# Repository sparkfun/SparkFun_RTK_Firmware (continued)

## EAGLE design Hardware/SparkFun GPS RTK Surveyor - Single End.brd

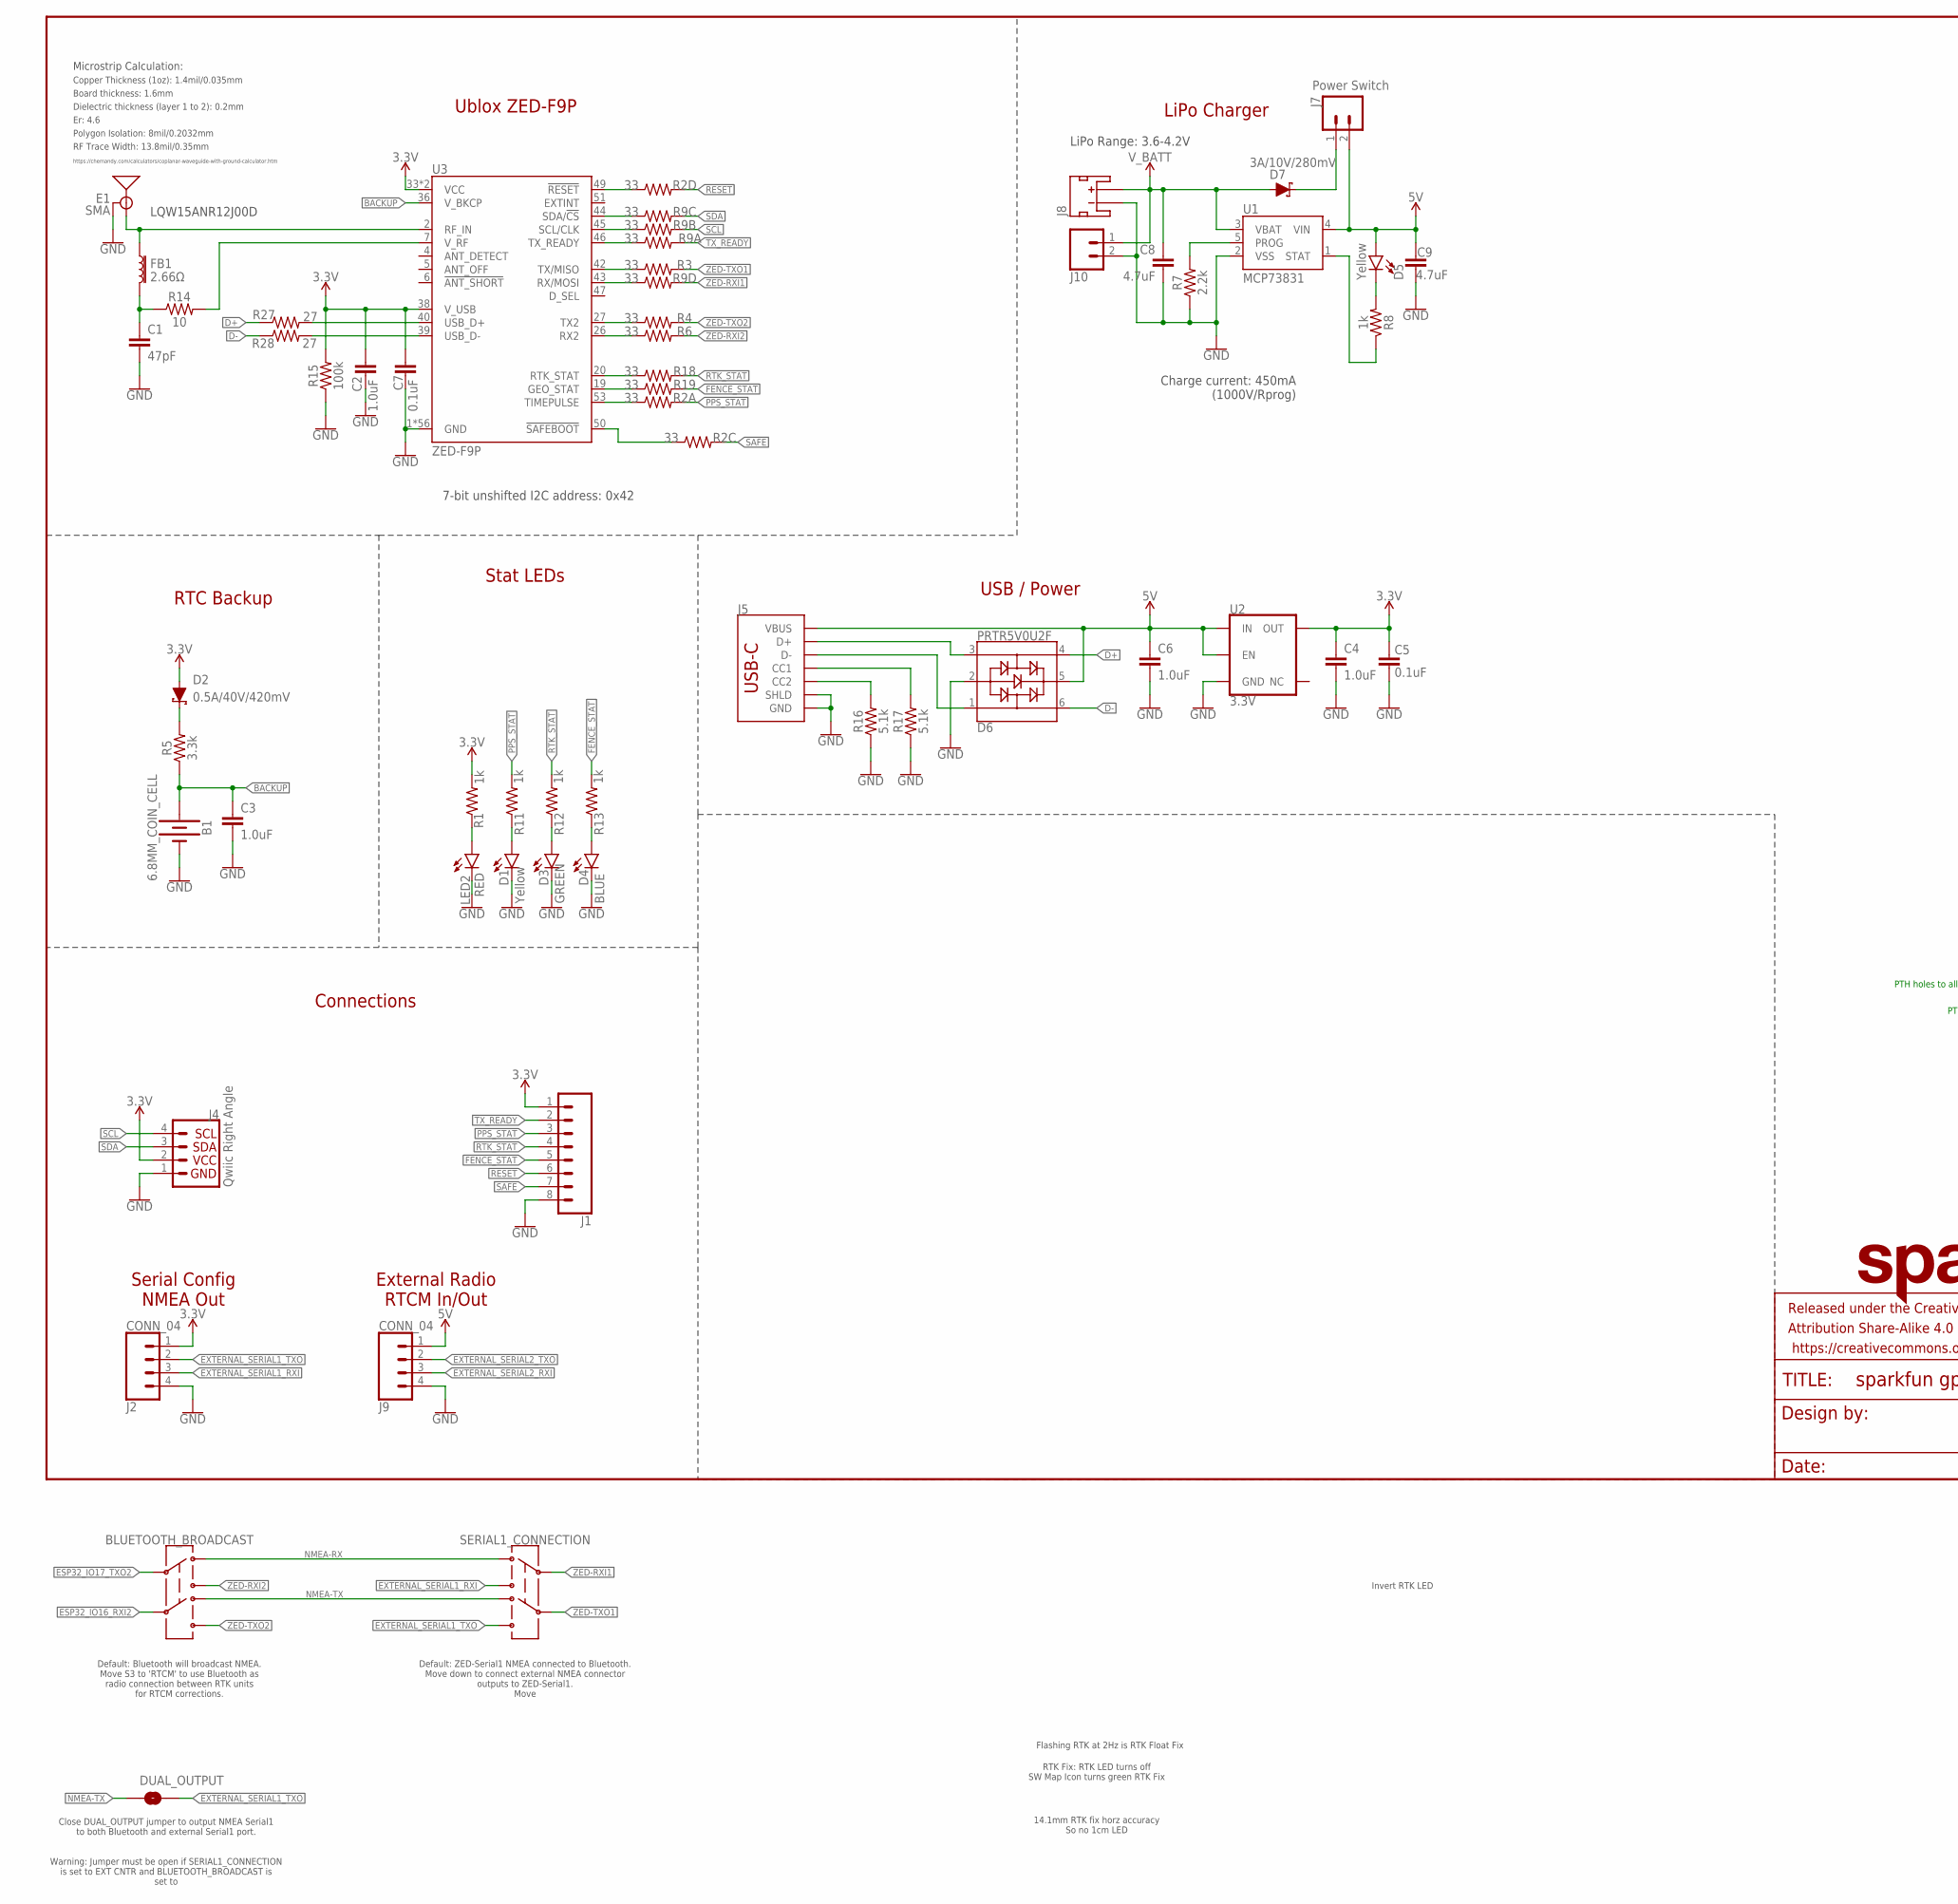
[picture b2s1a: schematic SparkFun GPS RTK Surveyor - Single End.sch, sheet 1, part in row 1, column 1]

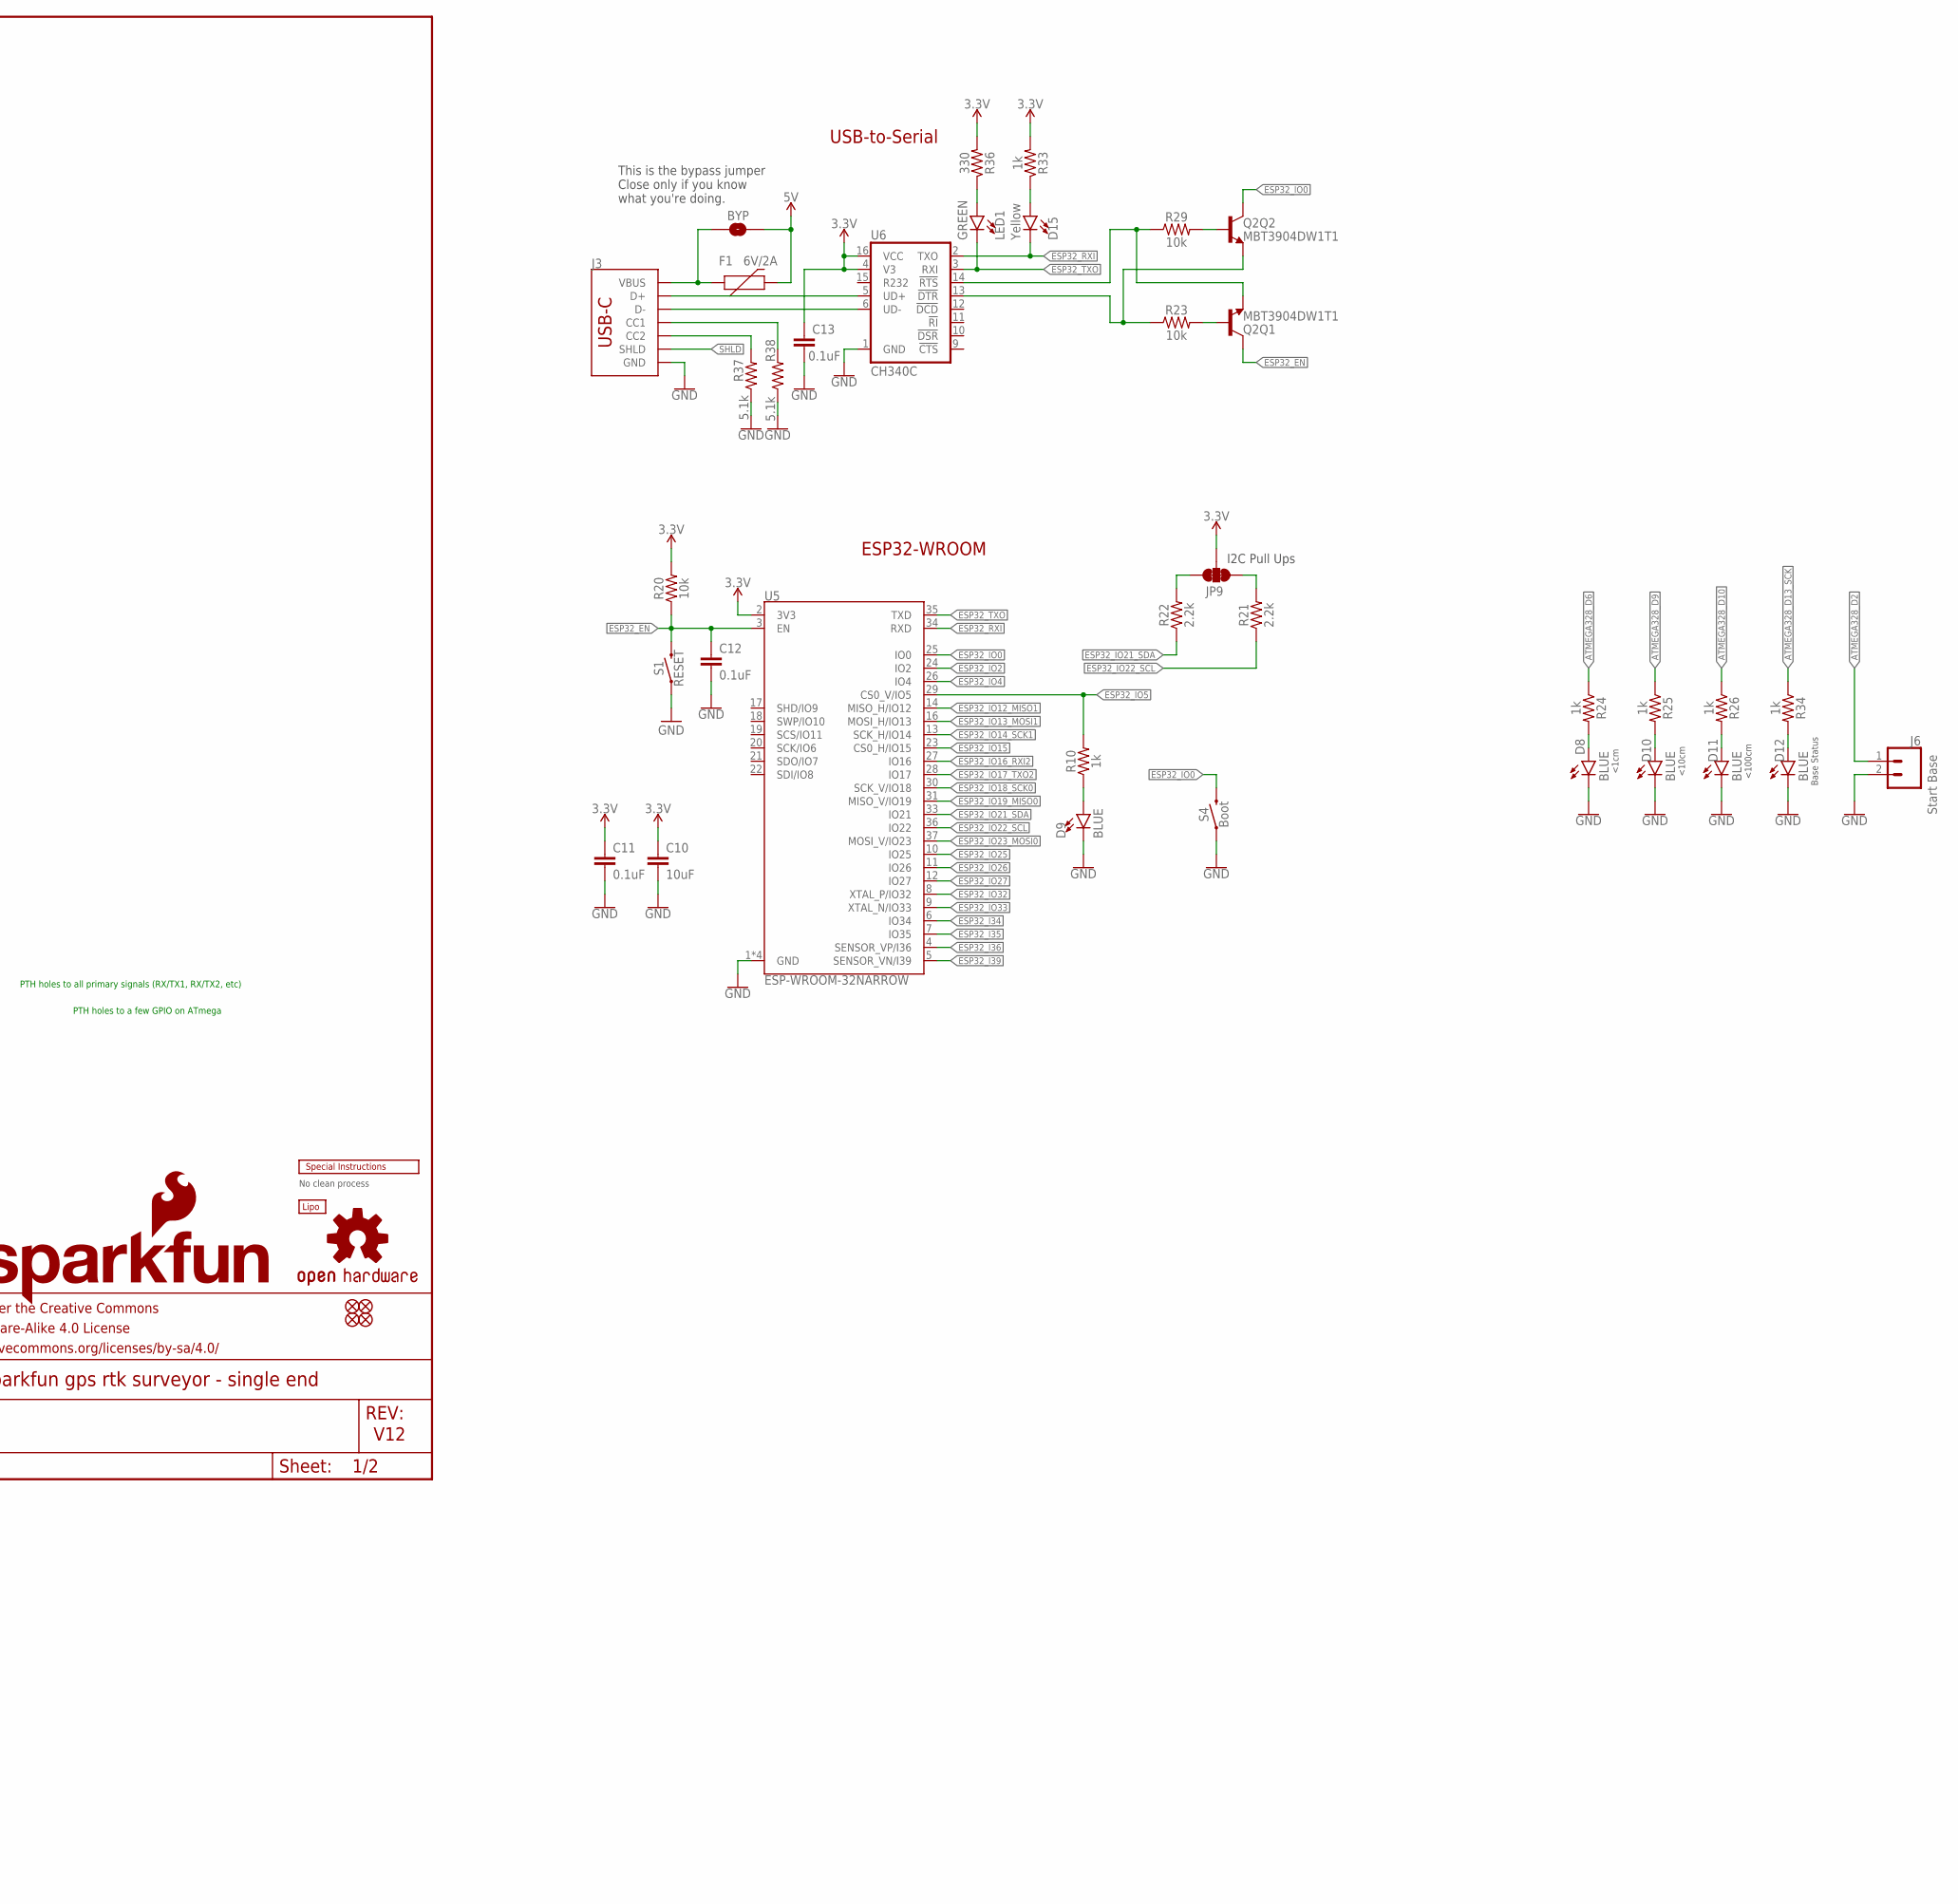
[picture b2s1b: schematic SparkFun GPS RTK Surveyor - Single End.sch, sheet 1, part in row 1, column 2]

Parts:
B1: 6.8MM_COIN_CELL; ML414H_IV01E
BLUETOOTH_BROADCAST: SWITCH-DPDT-SMD-AYZ0202; SWITCH_DPDT_SMD_AYZ0202
BT1: LIPO-OUTLINE1100; LIPO-1000
BYP: JUMPER-SMT_2_NO_SILK; SMT-JUMPER_2_NO_SILK
C1: 47pF; 0402
C2, C3, C4, C6: 1.0uF; 0603
C5, C7, C11, C12, C13: 0.1uF; 0603
C8, C9: 4.7uF; 0603
C10: 10uF; 0603
D1, D5, D15: Yellow; LED-0603
D2: 0.5A/40V/420mV; SOD-323
D3: GREEN; LED-0603
D4, D8, D9, D10, D11, D12: BLUE; LED-0603
D6: PRTR5V0U2F; SOT886
D7: 3A/10V/280mV; SOD-323
DUAL_OUTPUT: JUMPER-SMT_2_NO_SILK; SMT-JUMPER_2_NO_SILK
E1: SMA; SMA-EDGE-SMD
F1: 6V/2A; 1210
FB1: 2.66Ω; 0402-TIGHT
FRAME2: FRAME-LEDGER; CREATIVE_COMMONS
J1: CONN_08NO_SILK_DNP; 1X08_NO_SILK
J2, J9: CONN_04; JST-4-SMD-1.25MM-LOCKING
J3: USB-C; USB-C-16P-2LAYER-PADS
J4: Qwiic Right Angle; JST04_1MM_RA
J5: USB_C_2-LAYER_PADS; USB-C-16P-2LAYER-PADS
J6: Start Base; JST-2-SMD
J7: Power Switch; JST-2-SMD
J8: JST_2MM_MALE; JST-2-SMD
J10: CONN_021X02_NO_SILK; 1X02_NO_SILK
JP9: JUMPER-SMT_3_2-NC_TRACE_SILK; SMT-JUMPER_3_2-NC_TRACE_SILK
JP21, JP61, JP71, JP81: FIDUCIALUFIDUCIAL; MICRO-FIDUCIAL
LED1: GREEN; LED-0603
LED2: RED; LED-0603
LOGO1: OSHW-LOGOMINI; OSHW-LOGO-MINI
LOGO2: SFE_LOGO_NAME_FLAME.1_INCH; SFE_LOGO_NAME_FLAME_.1
Q2: MBT3904DW1T1; SC70-6
R1, R8, R10, R11, R12, R13, R24, R25, R26, R33, R34: 1k; 0603
R2, R9: 33; 1206_RA
R3, R4, R6, R18, R19: 33; 0603
R5: 3.3k; 0603
R7, R21, R22: 2.2k; 0603
R14: 10; 0603
R15: 100k; 0603
R16, R17, R37, R38: 5.1k; 0603
R20, R23, R29: 10k; 0603
R27, R28: 27; 0603
R36: 330; 0603
S1: RESET; TACTILE_SWITCH_SMD_6.0X3.5MM
S4: Boot; TACTILE_SWITCH_SMD_6.0X3.5MM
SERIAL1_CONNECTION: SWITCH-DPDT-SMD-AYZ0202; SWITCH_DPDT_SMD_AYZ0202
U1: MCP73831; SOT23-5
U2: 3.3V; SOT23-5
U3: ZED-F9P
U5: ESP-WROOM-32NARROW; ESP-WROOM-32-NARROW
U6: CH340C; SO016
U$2: SPECIAL_INSTRUCTIONS-ORDERING; ORDERING_INSTRUCTIONS

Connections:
3.3V: C2.1, C4.1, C5.2, C7.2, C10.1, C11.1, C13.1, D2.A, J1.1, J2.1, J4.2, JP9.2, R1.2, R15.2, R20.2, R33.2, R36.2, U2.5 (OUT), U3.33 (VCC), U3.34 (VCC), U3.38 (V_USB), U5.2 (3V3), U6.4 (V3), U6.16 (VCC)
5V: BYP.2, C6.1, C9.1, D5.A, D6.5, F1.2, J5.VBUS1 (VBUS), J5.VBUS2 (VBUS), J7.2 (1), J9.1, U1.4 (VIN), U2.1 (IN), U2.3 (EN)
!RESET: J1.6, R2.P5 (2)
!SAFE: J1.7, R2.P6 (2)
ANT_VCC: C1.1, FB1.2, R14.1
ATMEGA328_D2: J6.1 (2)
ATMEGA328_D6: R24.1
ATMEGA328_D9: R25.1
ATMEGA328_D10: R26.1
ATMEGA328_D13_SCK: R34.1
BACKUP: B1.+, C3.1, R5.1, U3.36 (V_BKCP)
CC1: J5.A5 (CC1), R17.2
CC2: J5.B5 (CC2), R16.2
CC3: J3.B5 (CC2), R37.2
CC4: J3.A5 (CC1), R38.2
CHG_LED: R8.1, U1.1 (STAT)
D+: D6.4, R27.1
D+1: J3.A6 (D+), J3.B6 (D+), U6.5 (UD+)
D-: D6.6, R28.1
D-1: J3.A7 (D-), J3.B7 (D-), U6.6 (UD-)
ESP32_!DTR: Q2.1 (E), R23.1, U6.13 (!DTR)
ESP32_!RTS: Q2.4 (E), R29.1, U6.14 (!RTS)
ESP32_EN: C12.1, Q2.3 (C), R20.1, S1.2, U5.3 (EN)
ESP32_I34: U5.6 (IO34)
ESP32_I35: U5.7 (IO35)
ESP32_I36: U5.4 (SENSOR_VP/I36)
ESP32_I39: U5.5 (SENSOR_VN/I39)
ESP32_IO0: Q2.6 (C), S4.2, U5.25 (IO0)
ESP32_IO2: U5.24 (IO2)
ESP32_IO4: U5.26 (IO4)
ESP32_IO5: R10.2, U5.29 (CS0_V/IO5)
ESP32_IO12_MISO1: U5.14 (MISO_H/IO12)
ESP32_IO13_MOSI1: U5.16 (MOSI_H/IO13)
ESP32_IO14_SCK1: U5.13 (SCK_H/IO14)
ESP32_IO15: U5.23 (CS0_H/IO15)
ESP32_IO16_RXI2: BLUETOOTH_BROADCAST.5, U5.27 (IO16)
ESP32_IO17_TXO2: BLUETOOTH_BROADCAST.2, U5.28 (IO17)
ESP32_IO18_SCK0: U5.30 (SCK_V/IO18)
ESP32_IO19_MISO0: U5.31 (MISO_V/IO19)
ESP32_IO21_SDA: R22.1, U5.33 (IO21)
ESP32_IO22_SCL: R21.1, U5.36 (IO22)
ESP32_IO23_MOSI0: U5.37 (MOSI_V/IO23)
ESP32_IO25: U5.10 (IO25)
ESP32_IO26: U5.11 (IO26)
ESP32_IO27: U5.12 (IO27)
ESP32_IO32: U5.8 (XTAL_P/IO32)
ESP32_IO33: U5.9 (XTAL_N/IO33)
ESP32_RXI: D15.C, U5.34 (RXD), U6.2 (TXO)
ESP32_TXO: LED1.C, U5.35 (TXD), U6.3 (RXI)
EXTERNAL_SERIAL1_RXI: J2.3, SERIAL1_CONNECTION.3
EXTERNAL_SERIAL1_TXO: DUAL_OUTPUT.2, J2.2, SERIAL1_CONNECTION.6
EXTERNAL_SERIAL2_RXI: J9.3
EXTERNAL_SERIAL2_TXO: J9.2
FENCE_STAT: J1.5, R13.2, R19.2
GND: B1.-, C1.2, C2.2, C3.2, C4.2, C5.1, C6.2, C7.1, C8.2, C9.2, C10.2, C11.2, C12.2, C13.2, D1.C, D3.C, D4.C, D6.2, D8.C, D9.C, D10.C, D11.C, D12.C, E1.GND@0 (GND), E1.GND@1 (GND), J1.8, J2.4, J3.GND, J3.GND2 (GND), J4.1, J5.GND, J5.GND2 (GND), J5.SHLD1 (SHLD), J5.SHLD2 (SHLD), J5.SHLD3 (SHLD), J5.SHLD4 (SHLD), J6.2 (1), J8.1 (-), J9.4, J10.2, LED2.C, R7.1, R15.1, R16.1, R17.1, R37.1, R38.1, S1.1, S4.1, U1.2 (VSS), U2.2 (GND), U3.1 (GND), U3.3 (GND), U3.12 (GND), U3.14 (GND), U3.32 (GND), U3.37 (GND), U3.41 (GND), U3.48 (GND), U3.55 (GND), U3.56 (GND), U3.57 (GND), U3.58 (GND), U3.59 (GND), U3.60 (GND), U3.61 (GND), U3.62 (GND), U3.63 (GND), U3.64 (GND), U3.65 (GND), U3.66 (GND), U3.67 (GND), U3.68 (GND), U3.69 (GND), U3.70 (GND), U3.71 (GND), U3.72 (GND), U3.73 (GND), U3.74 (GND), U3.75 (GND), U3.76 (GND), U3.77 (GND), U3.78 (GND), U3.79 (GND), U3.80 (GND), U3.81 (GND), U3.82 (GND), U3.83 (GND), U3.84 (GND), U3.85 (GND), U3.86 (GND), U3.87 (GND), U3.88 (GND), U3.89 (GND), U3.90 (GND), U3.91 (GND), U3.92 (GND), U3.93 (GND), U3.94 (GND), U3.95 (GND), U3.96 (GND), U3.97 (GND), U3.98 (GND), U3.99 (GND), U3.100 (GND), U3.101 (GND), U3.102 (GND), U5.1 (GND), U5.15 (GND), U5.38 (GND), U5.GND, U6.1 (GND)
GPS_ANT1: E1.SIG (SIGNAL), FB1.1, U3.2 (RF_IN)
unnamed: D3.A, R12.1
unnamed: D1.A, R11.1
unnamed: R7.2, U1.5 (PROG)
unnamed: D2.C, R5.2
unnamed: D4.A, R13.1
unnamed: D5.C, R8.2
unnamed: LED2.A, R1.1
unnamed: R27.2, U3.40 (USB_D+)
unnamed: R28.2, U3.39 (USB_D-)
unnamed: R14.2, U3.7 (V_RF)
unnamed: R6.1, U3.26 (RX2)
unnamed: R2.P4 (1), U3.49 (!RESET!)
unnamed: R2.P3 (1), U3.50 (!SAFEBOOT!)
unnamed: R18.1, U3.20 (RTK_STAT)
unnamed: R19.1, U3.19 (GEO_STAT)
unnamed: R9.P1 (1), U3.46 (TX_READY)
unnamed: D9.A, R10.1
unnamed: Q2.5 (B), R23.2
unnamed: Q2.2 (B), R29.2
unnamed: D8.A, R24.2
unnamed: D10.A, R25.2
unnamed: LED1.A, R36.1
unnamed: D11.A, R26.2
unnamed: D12.A, R34.2
unnamed: D15.A, R33.1
unnamed: BYP.1, F1.1, J3.VBUS1 (VBUS), J3.VBUS2 (VBUS)
NMEA-RX: BLUETOOTH_BROADCAST.1, SERIAL1_CONNECTION.1
NMEA-TX: BLUETOOTH_BROADCAST.4, DUAL_OUTPUT.1, SERIAL1_CONNECTION.4
PPS: R2.P1 (1), U3.53 (TIMEPULSE)
PPS_STAT: J1.3, R2.P8 (2), R11.2
RTK_STAT: J1.4, R12.2, R18.2
RXLV: R9.P4 (1), U3.43 (RX/MOSI)
SCL: J4.4, R9.P7 (2)
SCL_LV: R9.P2 (1), U3.45 (SCL/CLK)
SCL_PU1: JP9.1, R21.2
SDA: J4.3, R9.P6 (2)
SDA_LV: R9.P3 (1), U3.44 (SDA/!CS!)
SDA_PU1: JP9.3, R22.2
SHLD: J3.SHLD1 (SHLD), J3.SHLD2 (SHLD), J3.SHLD3 (SHLD), J3.SHLD4 (SHLD)
TX2_P: R4.1, U3.27 (TX2)
TXLV: R3.1, U3.42 (TX/MISO)
TX_READY: J1.2, R9.P8 (2)
UNP_D+: D6.3, J5.A6 (D+), J5.B6 (D+)
UNP_D-: D6.1, J5.A7 (D-), J5.B7 (D-)
VBATT_SWTICHED: D7.C, J7.1 (2)
V_BATT: C8.1, D7.A, J8.2 (+), J10.1, U1.3 (VBAT)
ZED-RXI1: R9.P5 (2), SERIAL1_CONNECTION.2
ZED-RXI2: BLUETOOTH_BROADCAST.3, R6.2
ZED-TXO1: R3.2, SERIAL1_CONNECTION.5
ZED-TXO2: BLUETOOTH_BROADCAST.6, R4.2

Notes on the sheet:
V12
7-bit unshifted I2C address: 0x42
Ublox ZED-F9P
RTC Backup
Stat LEDs
LQW15ANR12J00D
Board thickness: 1.6mm
Er: 4.6
Copper Thickness (1oz): 1.4mil/0.035mm
RF Trace Width: 13.8mil/0.35mm
Polygon Isolation: 8mil/0.2032mm
No clean process
Dielectric thickness (layer 1 to 2): 0.2mm
https://chemandy.com/calculators/coplanar-waveguide-with-ground-calculator.htm
Microstrip Calculation:
Connections
USB / Power
External Radio RTCM In/Out
Serial Config NMEA Out
LiPo Charger
LiPo Range: 3.6-4.2V
Charge current: 450mA (1000V/Rprog)
Base Status
<100cm
<10cm
<1cm
PTH holes to all primary signals (RX/TX1, RX/TX2, etc)
PTH holes to a few GPIO on ATmega
Default: Bluetooth will broadcast NMEA. Move S3 to 'RTCM' to use Bluetooth as radio connection between RTK units for RTCM corrections.
Default: ZED-Serial1 NMEA connected to Bluetooth. Move down to connect external NMEA connector outputs to ZED-Serial1. Move
Close DUAL_OUTPUT jumper to output NMEA Serial1 to both Bluetooth and external Serial1 port. Warning: Jumper must be open if SERIAL1_CONNECTION is set to EXT CNTR and BLUETOOTH_BROADCAST is set to
Flashing RTK at 2Hz is RTK Float Fix
RTK Fix: RTK LED turns off SW Map Icon turns green RTK Fix
Invert RTK LED
14.1mm RTK fix horz accuracy So no 1cm LED
ESP32-WROOM
I2C Pull Ups
USB-to-Serial
This is the bypass jumper Close only if you know what you're doing.

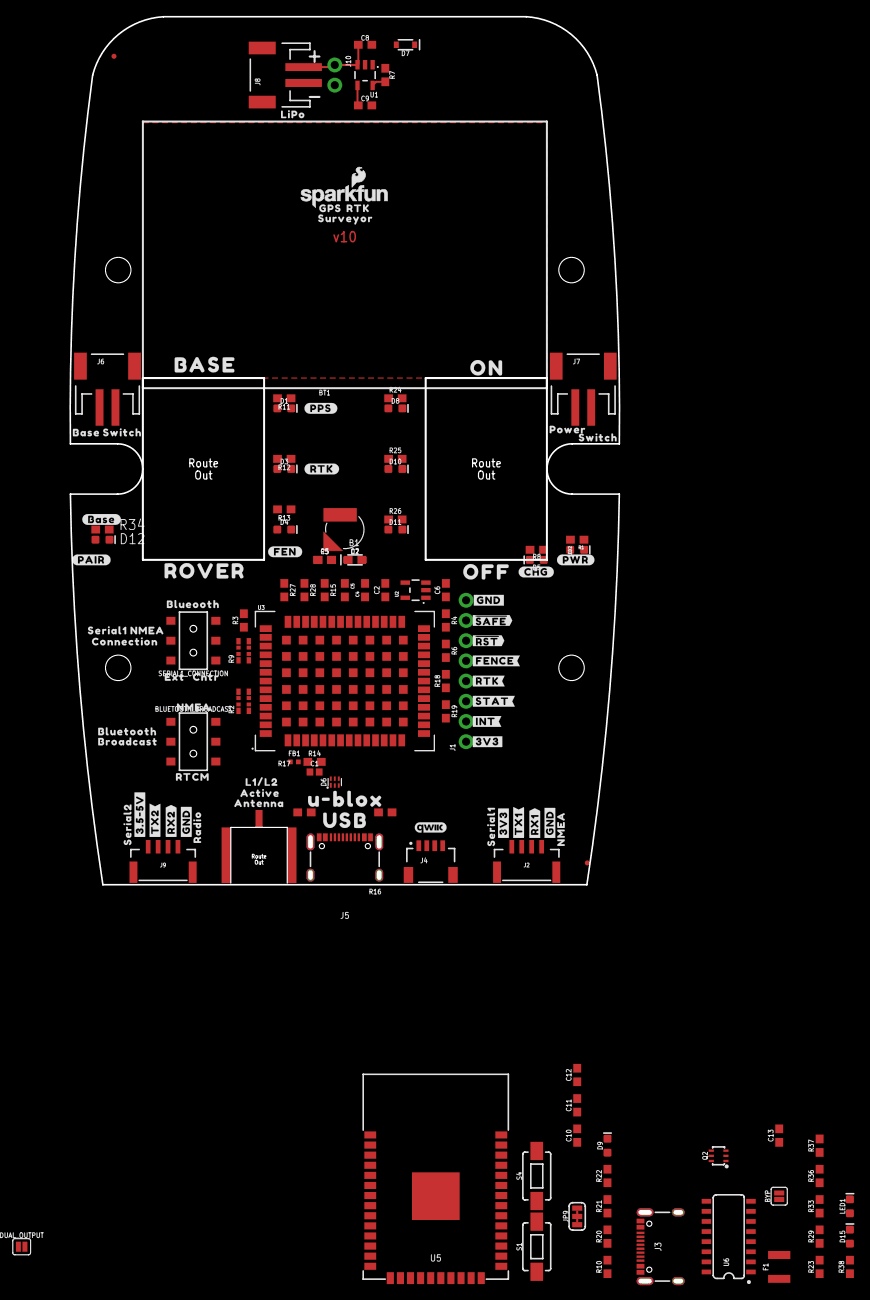
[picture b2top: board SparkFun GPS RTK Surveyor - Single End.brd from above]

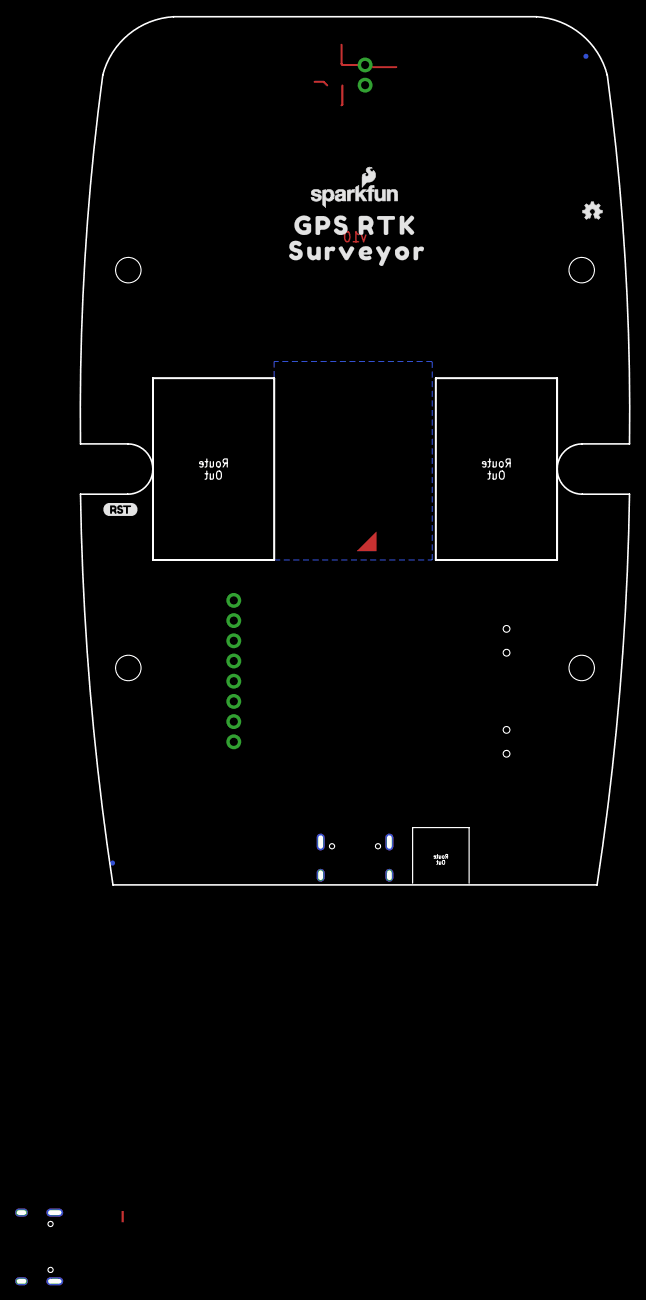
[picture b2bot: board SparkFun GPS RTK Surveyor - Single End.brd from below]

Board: 4 copper layers, 76.8 x 159.0 mm, 162 parts (7 on the bottom side), 81 nets.

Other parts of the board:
LOGO3: SFE_LOGO_NAME_FLAME.1_INCH; SFE_LOGO_NAME_FLAME_.1
U$1, U$38, U$48: #GND#0
U$3, U$34: ROCKER_SWITCH
U$4: #BASE#0
U$5: GPS0
U$6: ANTENNA0
U$7: GPS_RTK0
U$8: #CHG#0
U$9: _SURVEYOR3
U$10: #RTK#1
U$11: #STAT#0
U$12: #RTK#0
U$13, U$21: LIGHT_PIPE_3MM
U$14: SURVEYOR1
U$15: #FEN#0
U$16: RTK1
U$17: ##SAFE##5
U$18: ACTIVE0
U$19: L1#L21
U$20: #PAIR#0
U$22: BASE2
U$23: #3#5#5V#0
U$24: #PPS#1
U$25: #PWR#2
U$26: 1553DBK-ENCLOSURE
U$27: LIPO0
U$28: ##RST##4
U$29, U$63: SERIAL10
U$30: QWIIC_4MM
U$31: OFF1
U$32: #FENCE#3
U$33: #INT#0
U$35: U#BLOX0
U$36: USB1
U$37, U$47: #3V3#0
U$39: #RX2#2
U$40: #TX2#1
U$41: BLUETOOTH2
U$42: ON0
U$43: SERIAL20
U$44: ROVER3
U$45: #RX1#2
U$46: #TX1#1
U$49, U$52: NMEA1
U$50: RADIO0
U$51: BROADCAST3
U$53: RTCM0
U$54: BASE0
U$55, U$57: SWITCH1
U$56: POWER0
U$58: BLUEOOTH3
U$59: CNTR1
U$60: RST3
U$61: EXT0
U$62: NMEA2
U$64: CONNECTION1
